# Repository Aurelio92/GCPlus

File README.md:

# GC+ - What is it?
GC+ is a custom board that acts as a Gamecube controller with an upgradable firmware and custom features.
Video reference: https://www.youtube.com/watch?v=MTG2iqWmXx4

# How to make one?
You can order the PCBs from OshPark: https://oshpark.com/shared_projects/pEYojr6X

# Needed parts
A BOM is available in the Hardware folder

# How to flash it
Flash GC+.hex with MPLAB IPE (http://microchip.wikidot.com/ipe:installation) and a PICKIT v3.

# License

MIT License

Copyright (c) 2016 Aurelio Mannara

Permission is hereby granted, free of charge, to any person obtaining a copy
of this software and associated documentation files (the "Software"), to deal
in the Software without restriction, including without limitation the rights
to use, copy, modify, merge, publish, distribute, sublicense, and/or sell
copies of the Software, and to permit persons to whom the Software is
furnished to do so, subject to the following conditions:

The above copyright notice and this permission notice shall be included in all
copies or substantial portions of the Software.

THE SOFTWARE IS PROVIDED "AS IS", WITHOUT WARRANTY OF ANY KIND, EXPRESS OR
IMPLIED, INCLUDING BUT NOT LIMITED TO THE WARRANTIES OF MERCHANTABILITY,
FITNESS FOR A PARTICULAR PURPOSE AND NONINFRINGEMENT. IN NO EVENT SHALL THE
AUTHORS OR COPYRIGHT HOLDERS BE LIABLE FOR ANY CLAIM, DAMAGES OR OTHER
LIABILITY, WHETHER IN AN ACTION OF CONTRACT, TORT OR OTHERWISE, ARISING FROM,
OUT OF OR IN CONNECTION WITH THE SOFTWARE OR THE USE OR OTHER DEALINGS IN THE
SOFTWARE.

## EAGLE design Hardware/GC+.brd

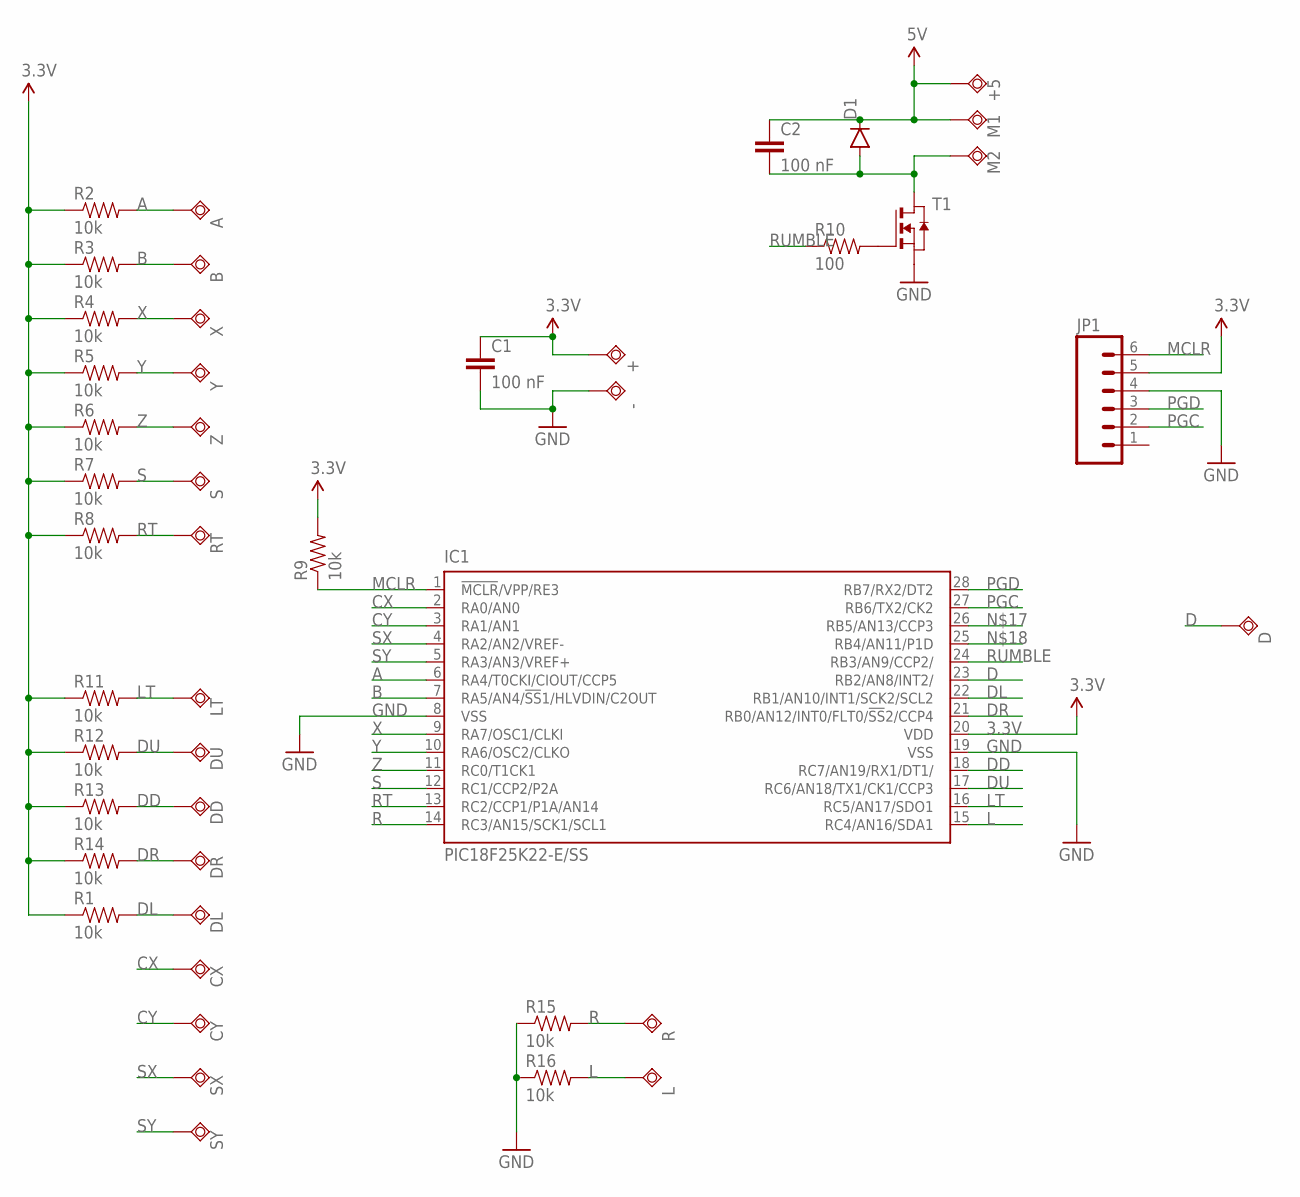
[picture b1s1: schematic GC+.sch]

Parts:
+, +5: TPSQTP10SQ; TP10SQ
-: TPSQTP10SQ; TP10SQ
A: TPSQTP10SQ; TP10SQ
B: TPSQTP10SQ; TP10SQ
C1, C2: 100 nF; 0805
CX: TPSQTP10SQ; TP10SQ
CY: TPSQTP10SQ; TP10SQ
D: TPSQTP10SQ; TP10SQ
D1: DIODEBAS16; SOD-323
DD: TPSQTP10SQ; TP10SQ
DL: TPSQTP10SQ; TP10SQ
DR: TPSQTP10SQ; TP10SQ
DU: TPSQTP10SQ; TP10SQ
IC1: PIC18F25K22-E/SS; SSOP28
JP1: M06SILK_FEMALE_PTH; 1X06
L: TPSQTP10SQ; TP10SQ
LT: TPSQTP10SQ; TP10SQ
M1, M2: TPSQTP10SQ; TP10SQ
R: TPSQTP10SQ; TP10SQ
R1, R2, R3, R4, R5, R6, R7, R8, R9, R11, R12, R13, R14, R15, R16: 10k; 0805
R10: 100; 0805
RT: TPSQTP10SQ; TP10SQ
S: TPSQTP10SQ; TP10SQ
SX: TPSQTP10SQ; TP10SQ
SY: TPSQTP10SQ; TP10SQ
T1: NMOSSOT23; SOT-23
X: TPSQTP10SQ; TP10SQ
Y: TPSQTP10SQ; TP10SQ
Z: TPSQTP10SQ; TP10SQ

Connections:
3.3V: +.TP, C1.1, IC1.20 (VDD), JP1.5, R1.1, R2.1, R3.1, R4.1, R5.1, R6.1, R7.1, R8.1, R9.2, R11.1, R12.1, R13.1, R14.1
5V: +5.TP, C2.1, D1.C, M1.TP
A: A.TP, IC1.6 (RA4/T0CKI/CIOUT/CCP5), R2.2
B: B.TP, IC1.7 (RA5/AN4/!SS!1/HLVDIN/C2OUT), R3.2
CX: CX.TP, IC1.2 (RA0/AN0)
CY: CY.TP, IC1.3 (RA1/AN1)
D: D.TP, IC1.23 (RB2/AN8/INT2/)
DD: DD.TP, IC1.18 (RC7/AN19/RX1/DT1/), R13.2
DL: DL.TP, IC1.22 (RB1/AN10/INT1/SCK2/SCL2), R1.2
DR: DR.TP, IC1.21 (RB0/AN12/INT0/FLT0/!SS!2/CCP4), R14.2
DU: DU.TP, IC1.17 (RC6/AN18/TX1/CK1/CCP3), R12.2
GND: -.TP, C1.2, IC1.8 (VSS), IC1.19 (VSS), JP1.4, R15.1, R16.1, T1.2 (S)
L: IC1.15 (RC4/AN16/SDA1), L.TP, R16.2
LT: IC1.16 (RC5/AN17/SDO1), LT.TP, R11.2
MCLR: IC1.1 (!MCLR!/VPP/RE3), JP1.6, R9.1
unnamed: R10.2, T1.3 (G)
unnamed: C2.2, D1.A, M2.TP, T1.1 (D)
PGC: IC1.27 (RB6/TX2/CK2), JP1.2
PGD: IC1.28 (RB7/RX2/DT2), JP1.3
R: IC1.14 (RC3/AN15/SCK1/SCL1), R.TP, R15.2
RT: IC1.13 (RC2/CCP1/P1A/AN14), R8.2, RT.TP
RUMBLE: IC1.24 (RB3/AN9/CCP2/), R10.1
S: IC1.12 (RC1/CCP2/P2A), R7.2, S.TP
SX: IC1.4 (RA2/AN2/VREF-), SX.TP
SY: IC1.5 (RA3/AN3/VREF+), SY.TP
X: IC1.9 (RA7/OSC1/CLKI), R4.2, X.TP
Y: IC1.10 (RA6/OSC2/CLKO), R5.2, Y.TP
Z: IC1.11 (RC0/T1CK1), R6.2, Z.TP

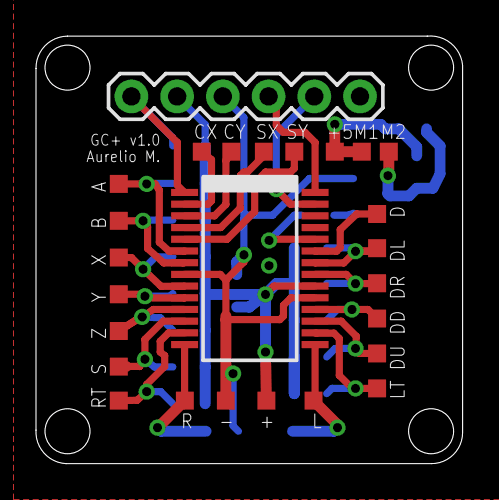
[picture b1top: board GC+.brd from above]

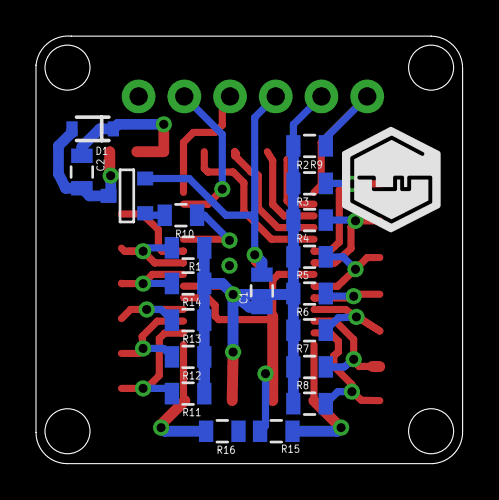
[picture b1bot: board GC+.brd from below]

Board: 2 copper layers, 23.7 x 23.8 mm, 47 parts (20 on the bottom side), 28 nets.

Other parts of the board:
U$1: LOGOGC

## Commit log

2017-01-07 First public release
2017-01-07 Typo fix in the readme
2017-01-07 Fixed the BOM

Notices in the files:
parts and their libraries:
SparkFun-Passives: Licensing: Creative Commons ShareAlike 4.0 International - https://creativecommons.org/licenses/by-sa/4.0
